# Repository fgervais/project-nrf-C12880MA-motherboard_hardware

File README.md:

# C12880MA Motherboard (Hardware)

## Schematic

[project-nrf-C12880MA-motherboard.pdf](project-nrf-C12880MA-motherboard.pdf)

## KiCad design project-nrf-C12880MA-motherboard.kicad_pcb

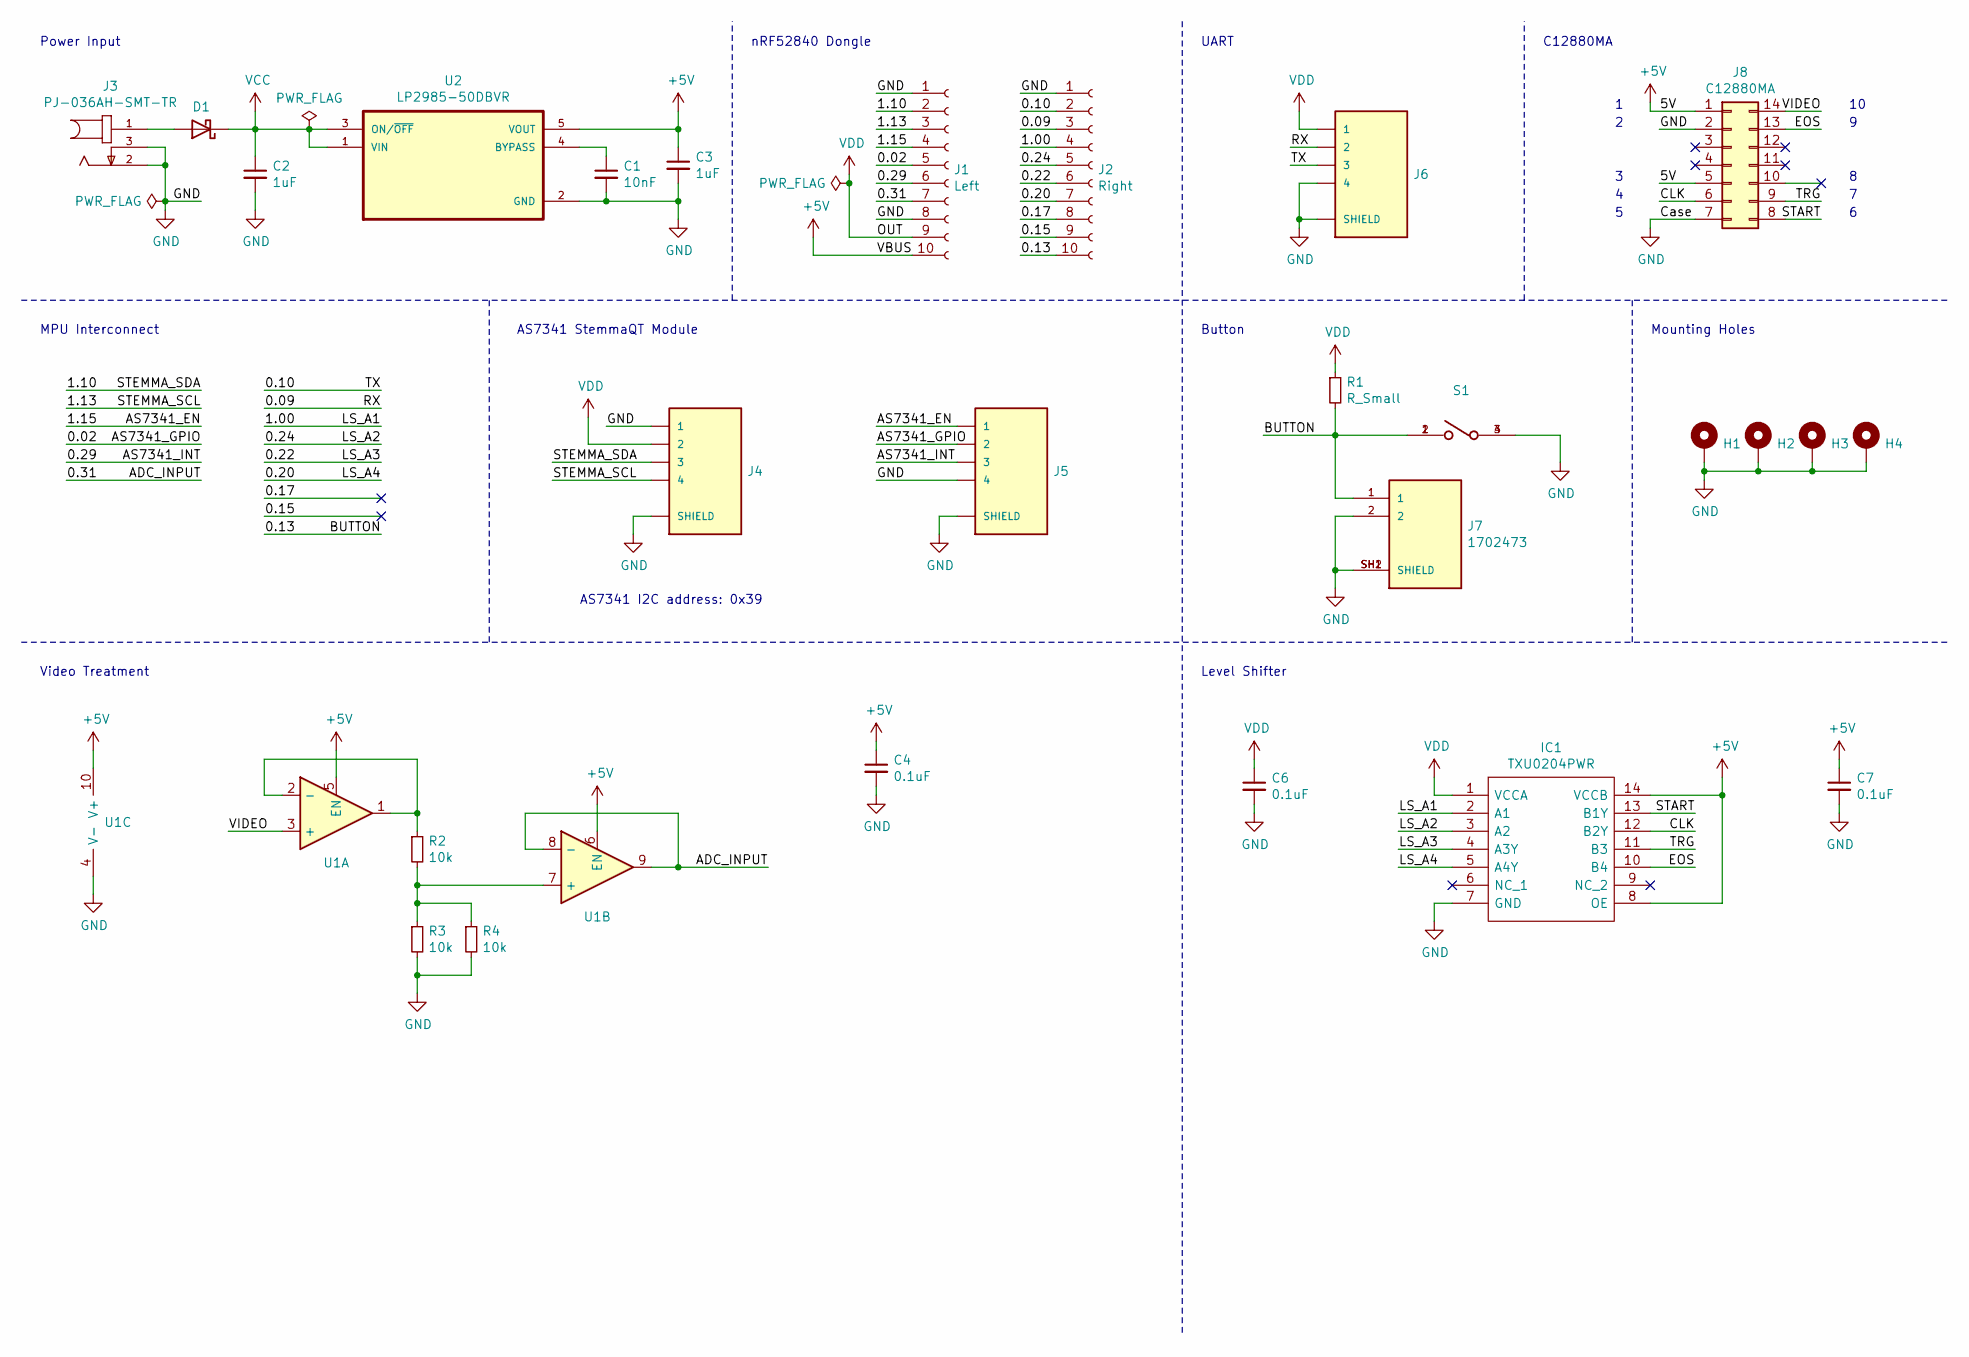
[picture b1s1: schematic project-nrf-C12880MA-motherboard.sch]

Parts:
C1: 10nF; C_0603_1608Metric
C2, C3: 1uF; C_0805_2012Metric
C4, C6, C7: 0.1uF; C_0603_1608Metric
D1: D_Schottky; DIO_CUS520,H3F
H1, H2, H3, H4: MountingHole_Pad; MountingHole_2.7mm_M2.5_Pad_Via
IC1: TXU0204PWR; SOP65P640X120-14N; Manufacturer_Part_Number TXU0204PWR; Mouser Part Number 595-TXU0204PWR
J1: Left; PinSocket_1x10_P2.54mm_Vertical_SMD_Pin1Right
J2: Right; PinSocket_1x10_P2.54mm_Vertical_SMD_Pin1Right
J3: PJ-036AH-SMT-TR; CUI_PJ-036AH-SMT-TR; DIGI-KEY_PART_NUMBER CP-036AHPJCT-ND
J4, J5, J6: SM04B-SRSS-TB(LF)(SN); JST_SM04B-SRSS-TB(LF)(SN)
J7: 1702473; PHOENIX_1702473; PARTREV MAR20,2012
J8: C12880MA; DIP-14_W7.62mm_SMDSocket_SmallPads
R1: R_Small; R_0603_1608Metric
R2, R3, R4: 10k; R_0603_1608Metric
S1: B3FS-1010P; SW_B3FS-1010P
U1: Opamp_Dual; SOP50P490X110-10N
U2: LP2985-50DBVR; SOT95P280X145-5N

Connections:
+5V: C3.1, C4.1, C7.1, IC1.8 (OE), IC1.14 (VCCB), J1.10, J8.1, J8.5, U1.5 (EN), U1.6 (EN), U1.10 (V+), U2.5 (VOUT)
/0.02: J1.5, J5.2
/0.09: J2.3, J6.2
/0.10: J2.2, J6.3
/0.13: J2.10, J7.1, R1.2, S1.1, S1.2
/0.15: J2.9
/0.17: J2.8
/0.20: IC1.5 (A4Y), J2.7
/0.22: IC1.4 (A3Y), J2.6
/0.24: IC1.3 (A2), J2.5
/0.29: J1.6, J5.3
/0.31: J1.7, U1.8 (-), U1.9
/1.00: IC1.2 (A1), J2.4
/1.10: J1.2, J4.3
/1.13: J1.3, J4.4
/1.15: J1.4, J5.1
/CLK: IC1.12 (B2Y), J8.6
/EOS: IC1.10 (B4), J8.13
/START: IC1.13 (B1Y), J8.8
/TRG: IC1.11 (B3), J8.9
/VIDEO: J8.14, U1.3 (+)
GND: C1.2, C2.2, C3.2, C4.2, C6.2, C7.2, H1.1, H2.1, H3.1, H4.1, IC1.7 (GND), J1.1, J1.8, J2.1, J3.2, J3.3, J4.1, J4.S1 (SHIELD), J4.S2 (SHIELD), J5.4, J5.S1 (SHIELD), J5.S2 (SHIELD), J6.4, J6.S1 (SHIELD), J6.S2 (SHIELD), J7.2, J7.SH1 (SHIELD), J7.SH2 (SHIELD), J8.2, J8.7, R3.2, R4.2, S1.3, S1.4, U1.4 (V-), U2.2 (GND)
unnamed: C1.1, U2.4 (BYPASS)
unnamed: D1.2 (A), J3.1
unnamed: R2.1, U1.1, U1.2 (-)
unnamed: R2.2, R3.1, R4.1, U1.7 (+)
VCC: C2.1, D1.1 (K), U2.1 (VIN), U2.3 (ON/~OFF)
VDD: C6.1, IC1.1 (VCCA), J1.9, J4.2, J6.1, R1.1

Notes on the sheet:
AS7341 I2C address: 0x39
nRF52840 Dongle
UART
Power Input
C12880MA
Button
AS7341 StemmaQT Module
MPU Interconnect
Video Treatment
Level Shifter
Mounting Holes

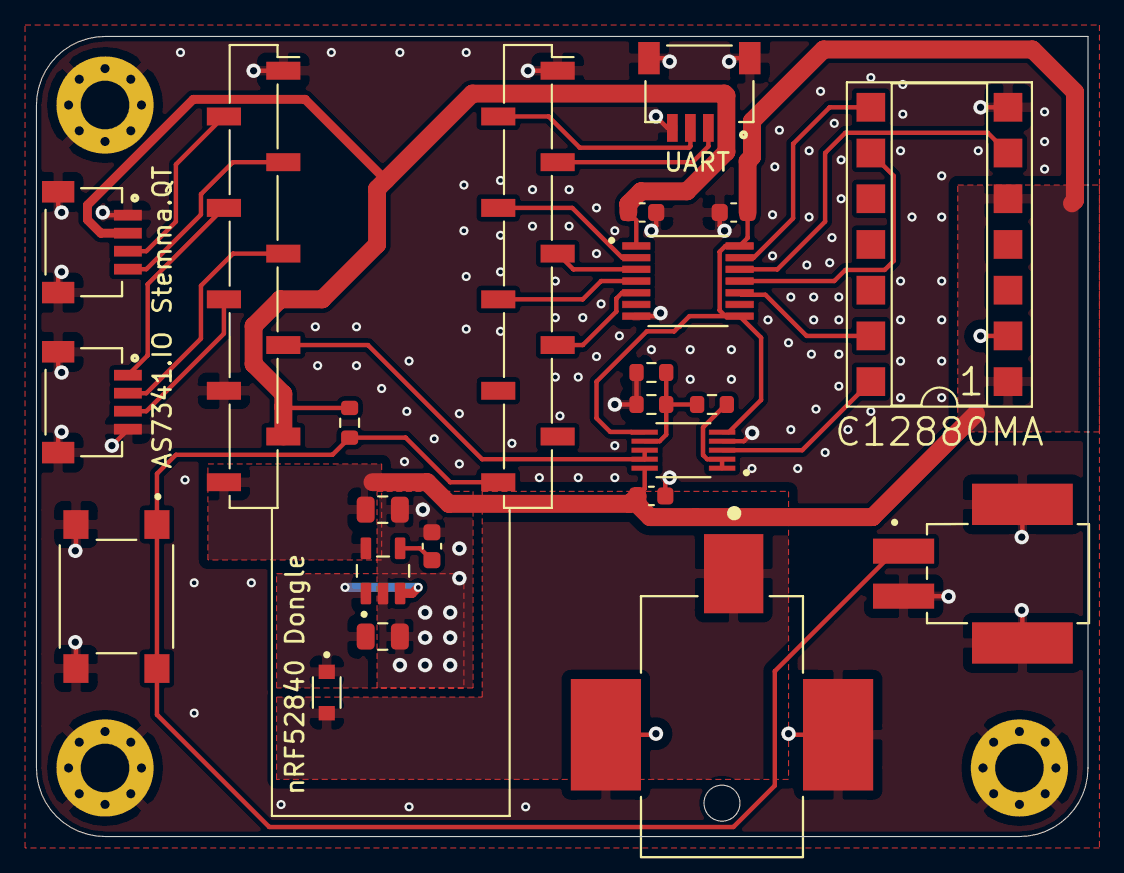
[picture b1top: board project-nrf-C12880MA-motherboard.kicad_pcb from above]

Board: 2 copper layers, 58.4 x 44.5 mm, 26 parts (0 on the bottom side), 26 nets.

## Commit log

2022-04-10 Add the library module
2022-04-10 Add gitignore
2022-04-10 Add blank project
2022-04-10 Import sch stuff from project-nrf-thread-switch
2022-04-11 Add PHOENIX_1702473
2022-04-11 Setup power input, add most components
2022-04-14 Schematic done
2022-04-14 Fix the CUS520,H3F diode
2022-04-14 Started routing
2022-04-14 First placement
2022-04-14 Placement 2
2022-04-15 Routing
2022-04-15 Add Schematic
2022-04-15 Add README
2022-04-22 Add C12880MA socket
2022-04-22 Change level-shifter to TXU0204
2022-04-23 Change ADC to dual OpAmp
2022-04-23 Placement done
2022-04-23 Routing done
2022-04-23 Add C12880MA render
2022-04-23 Add version of previous commit
2022-04-24 Update schematic
2022-04-24 Reroute regulator section and fix cap footprint (0603->0805)
2022-04-25 One more save on close
2022-04-28 Swap the regulator for the LP2985-50
2022-05-04 Use https url for kicad library submodule
